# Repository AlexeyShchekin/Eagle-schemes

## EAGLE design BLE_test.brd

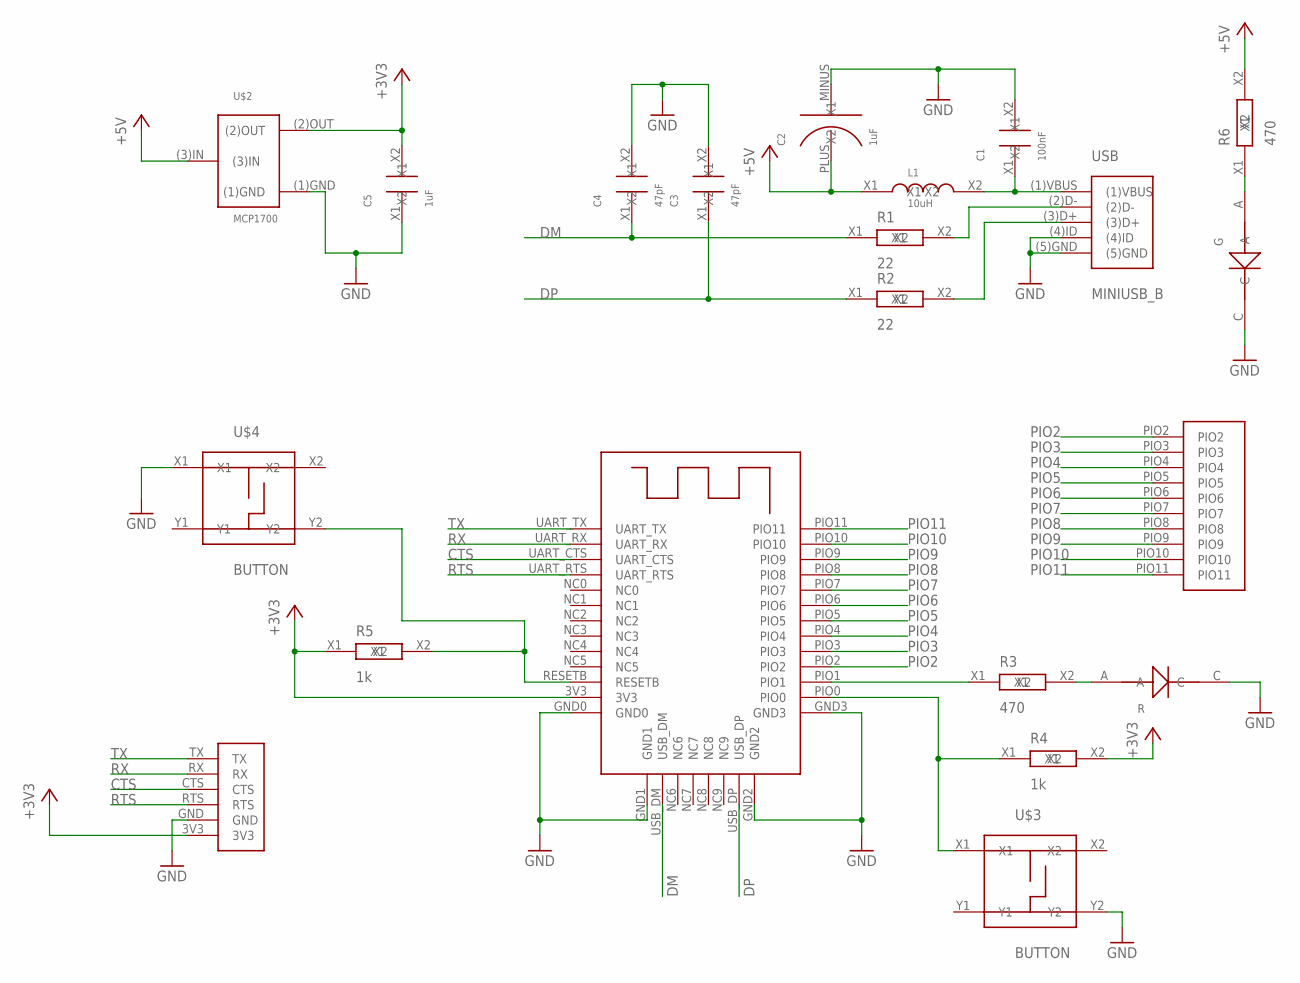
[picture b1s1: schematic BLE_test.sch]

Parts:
C1: 100nF; SMD_2.1X1.25
C2: 1uF; C_SMD_TA_A
C3, C4: 47pF; SMD_2.1X1.25
C5: 1uF; SMD_2.1X1.25
G: LED0805; SMD0805
L1: 10uH; SMD_2.1X1.25
R: LED0805; SMD0805
R1, R2: 22; SMD_2.1X1.25
R3, R6: 470; SMD_2.1X1.25
R4, R5: 1k; SMD_2.1X1.25
U$1: BLE_HM10
U$2: MCP1700
U$3, U$4: BUTTON
U$5: PIN6
U$7: PIO_10
USB: MINIUSB_B

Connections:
+3V3: C5.X2, R4.X2, R5.X1, U$1.3V3, U$2.(2)OUT, U$5.3V3
+5V: C2.PLUS (X1), L1.X1, R6.X2, U$2.(3)IN
CTS: U$1.UART_CTS, U$5.CTS
DM: C4.X1, R1.X1, U$1.USB_DM
DP: C3.X1, R2.X1, U$1.USB_DP
GND: C1.X2, C2.MINUS (X2), C3.X2, C4.X2, C5.X1, G.C, R.C, U$1.GND0, U$1.GND1, U$1.GND2, U$1.GND3, U$2.(1)GND, U$3.Y2, U$4.X1, U$5.GND, USB.(4)ID, USB.(5)GND
unnamed: C1.X1, L1.X2, USB.(1)VBUS
unnamed: R2.X2, USB.(3)D+
unnamed: R1.X2, USB.(2)D-
unnamed: R3.X1, U$1.PIO1
unnamed: R.A, R3.X2
unnamed: R4.X1, U$1.PIO0, U$3.X1
unnamed: G.A, R6.X1
unnamed: R5.X2, U$1.RESETB, U$4.Y2
PIO2: U$1.PIO2, U$7.PIO2
PIO3: U$1.PIO3, U$7.PIO3
PIO4: U$1.PIO4, U$7.PIO4
PIO5: U$1.PIO5, U$7.PIO5
PIO6: U$1.PIO6, U$7.PIO6
PIO7: U$1.PIO7, U$7.PIO7
PIO8: U$1.PIO8, U$7.PIO8
PIO9: U$1.PIO9, U$7.PIO9
PIO10: U$1.PIO10, U$7.PIO10
PIO11: U$1.PIO11, U$7.PIO11
RTS: U$1.UART_RTS, U$5.RTS
RX: U$1.UART_RX, U$5.RX
TX: U$1.UART_TX, U$5.TX

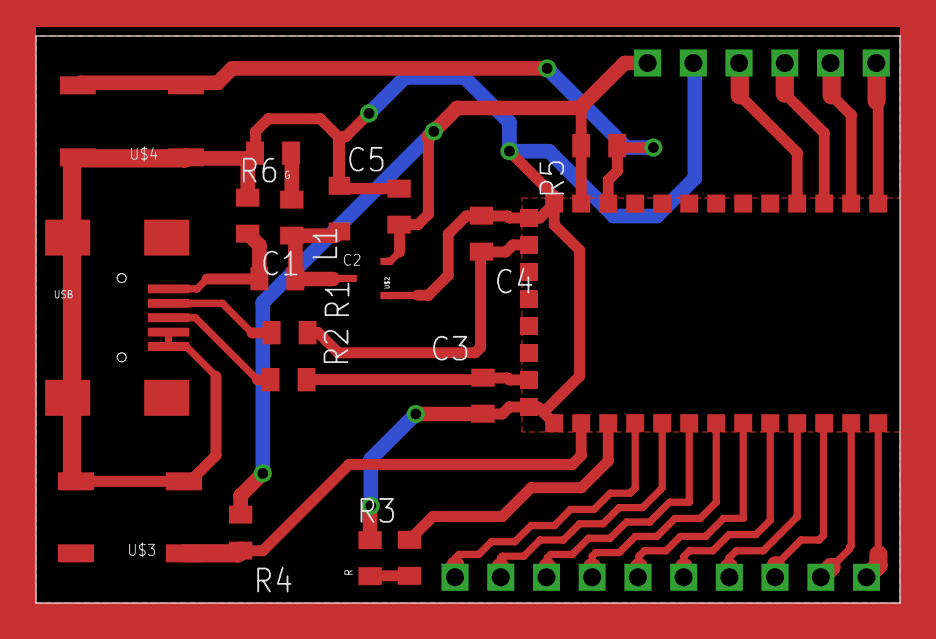
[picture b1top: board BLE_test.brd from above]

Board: 2 copper layers, 48.0 x 31.5 mm, 21 parts (0 on the bottom side), 27 nets.

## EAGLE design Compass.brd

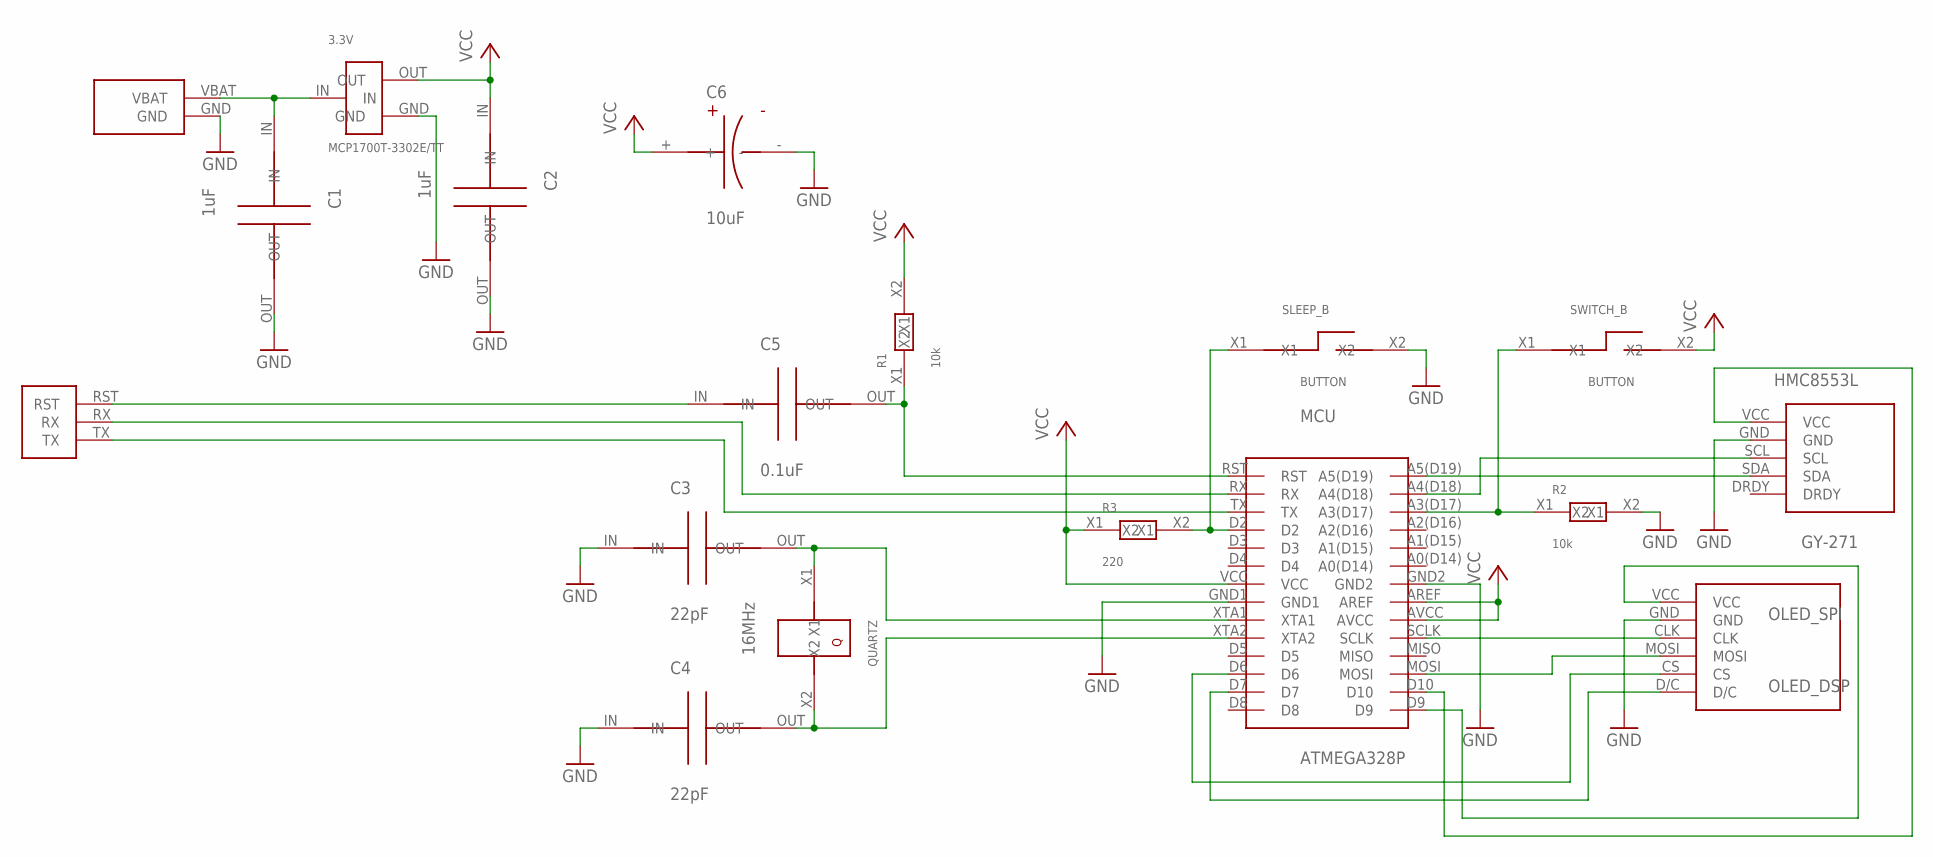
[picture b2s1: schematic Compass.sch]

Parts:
3.3V: MCP1700T-3302E/TT
C1, C2: 1uF; C_CER_5MM
C3, C4: 22pF; C_CER_5MM
C5: 0.1uF; C_CER_5MM
C6: 10uF; C_ELT_2MM
HMC8553L: GY-271
MCU: ATMEGA328P; DIP28
OLED_SPI: OLED_DSP
QUARTZ: 16MHz; Q_16
R1, R2: 10k; R_6X2
R3: 220; R_6X2
SLEEP_B: BUTTON
SWITCH_B: BUTTON
U$1: PROG_PLUG
U$6: BAT_PLUG

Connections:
GND: 3.3V.GND, C1.OUT, C2.OUT, C3.IN, C4.IN, C6.-, HMC8553L.GND, MCU.GND1, MCU.GND2, OLED_SPI.GND, R2.X2, SLEEP_B.X2, U$6.GND
unnamed: MCU.SCLK, OLED_SPI.CLK
unnamed: MCU.MOSI, OLED_SPI.MOSI
unnamed: HMC8553L.SDA, MCU.A5(D19)
unnamed: HMC8553L.SCL, MCU.A4(D18)
unnamed: 3.3V.IN, C1.IN, U$6.VBAT
unnamed: MCU.D9, OLED_SPI.VCC
unnamed: C3.OUT, MCU.XTA1, QUARTZ.X1
unnamed: C4.OUT, MCU.XTA2, QUARTZ.X2
unnamed: MCU.D6, OLED_SPI.CS
unnamed: MCU.D7, OLED_SPI.D/C
unnamed: HMC8553L.VCC, MCU.D10
unnamed: C5.OUT, MCU.RST, R1.X1
unnamed: MCU.D2, R3.X2, SLEEP_B.X1
unnamed: MCU.A3(D17), R2.X1, SWITCH_B.X1
unnamed: C5.IN, U$1.RST
unnamed: MCU.RX, U$1.RX
unnamed: MCU.TX, U$1.TX
VCC: 3.3V.OUT, C2.IN, C6.+, MCU.AREF, MCU.AVCC, MCU.VCC, R1.X2, R3.X1, SWITCH_B.X2

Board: 2 copper layers, 18 parts (0 on the bottom side), 19 nets, no tracks yet.

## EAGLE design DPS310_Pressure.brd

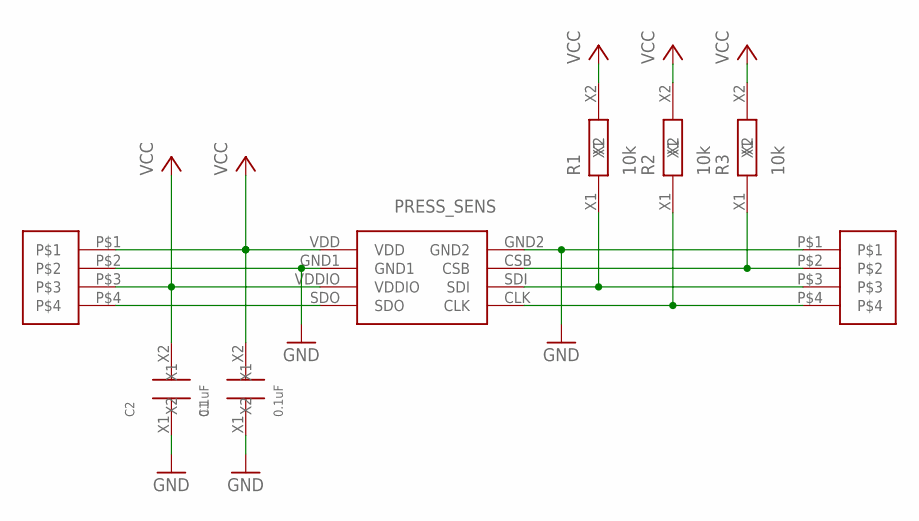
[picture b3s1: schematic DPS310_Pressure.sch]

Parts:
C1, C2: 0.1uF; SMD_2.1X1.25
PRESS_SENS: DPS310_INFINEON; DSP310
R1, R2, R3: 10k; SMD_2.1X1.25
U$1, U$2: 4-PIN-NONAME

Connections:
GND: C1.X1, C2.X1, PRESS_SENS.GND1, PRESS_SENS.GND2, U$1.P$1, U$2.P$2
unnamed: PRESS_SENS.CSB, R3.X1, U$1.P$2
unnamed: PRESS_SENS.SDI, R1.X1, U$1.P$3
unnamed: PRESS_SENS.CLK, R2.X1, U$1.P$4
unnamed: PRESS_SENS.SDO, U$2.P$4
VCC: C1.X2, C2.X2, PRESS_SENS.VDD, PRESS_SENS.VDDIO, R1.X2, R2.X2, R3.X2, U$2.P$1, U$2.P$3

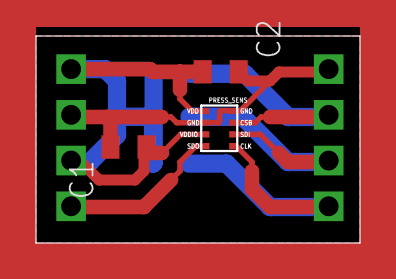
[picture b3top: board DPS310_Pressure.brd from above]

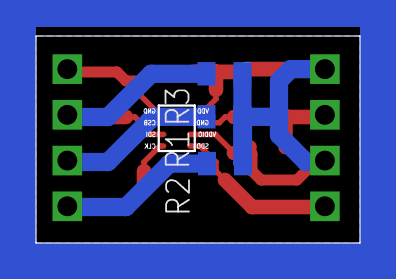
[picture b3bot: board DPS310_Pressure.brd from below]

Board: 2 copper layers, 18.0 x 11.5 mm, 8 parts (3 on the bottom side), 6 nets.

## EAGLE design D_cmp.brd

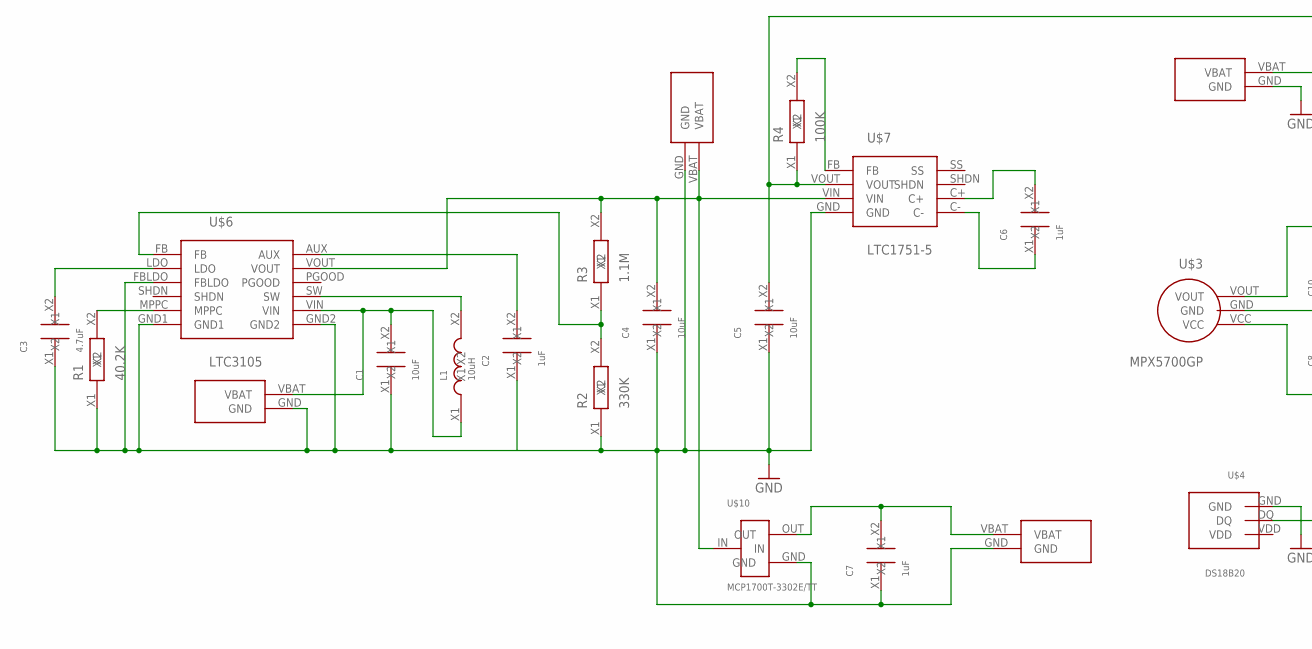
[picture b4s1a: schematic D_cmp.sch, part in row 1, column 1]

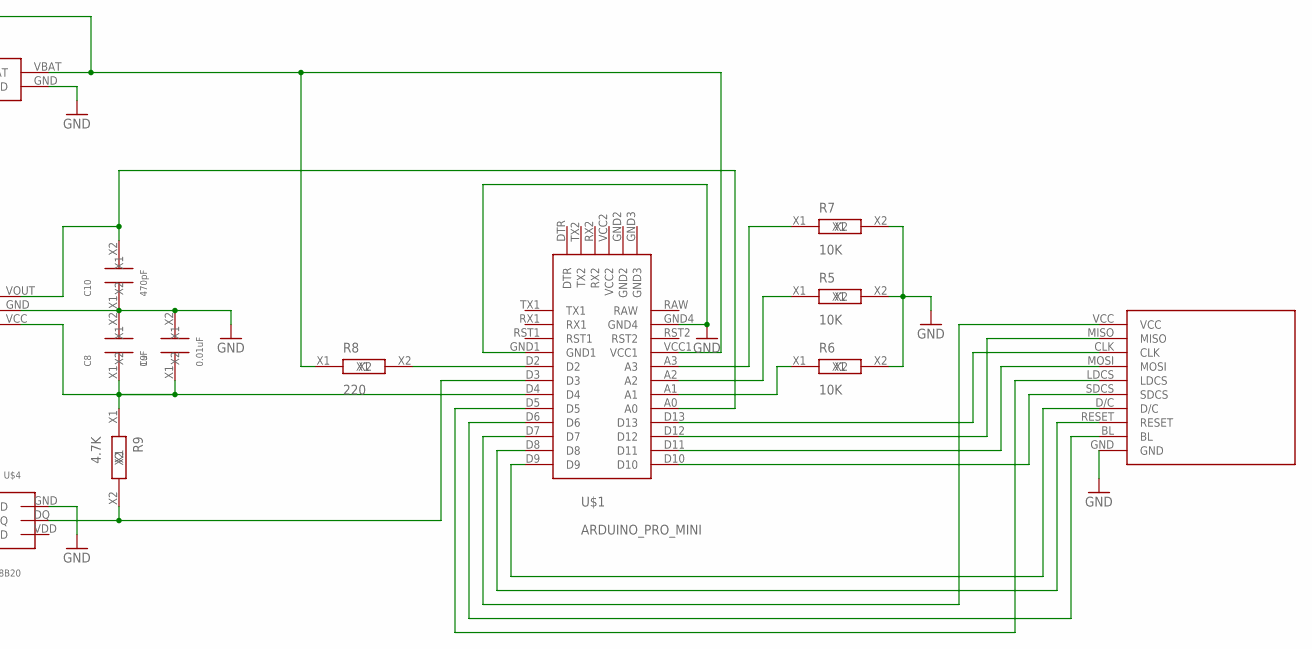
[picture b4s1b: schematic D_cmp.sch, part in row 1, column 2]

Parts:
C1, C4, C5: 10uF; SMD_2.1X1.25
C2, C6, C7, C8: 1uF; SMD_2.1X1.25
C3: 4.7uF; SMD_2.1X1.25
C9: 0.01uF; SMD_2.1X1.25
C10: 470pF; SMD_2.1X1.25
L1: 10uH; SMD_2.1X1.25
R1: 40.2K; SMD_2.1X1.25
R2: 330K; SMD_2.1X1.25
R3: 1.1M; SMD_2.1X1.25
R4: 100K; SMD_2.1X1.25
R5, R6, R7: 10K; SMD_2.1X1.25
R8: 220; SMD_2.1X1.25
R9: 4.7K; SMD_2.1X1.25
U$1: ARDUINO_PRO_MINI
U$2: TFT_LCD
U$3: MPX5700GP
U$4: DS18B20
U$5, U$8, U$9, U$11: BAT_PLUG
U$6: LTC3105
U$7: LTC1751-5
U$10: MCP1700T-3302E/TT

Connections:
GND: C1.X1, C2.X1, C3.X1, C4.X1, C5.X1, C7.X1, C8.X2, C9.X2, C10.X1, R1.X1, R2.X1, R5.X2, R6.X2, R7.X2, U$1.GND1, U$1.GND4, U$2.GND, U$3.GND, U$4.GND, U$5.GND, U$6.FBLDO, U$6.GND1, U$6.GND2, U$7.GND, U$8.GND, U$9.GND, U$10.GND, U$11.GND
unnamed: U$1.D9, U$2.D/C
unnamed: U$1.D8, U$2.RESET
unnamed: U$1.D10, U$2.SDCS
unnamed: U$1.D11, U$2.MOSI
unnamed: U$1.D12, U$2.MISO
unnamed: U$1.D13, U$2.CLK
unnamed: U$1.D7, U$2.VCC
unnamed: U$1.D6, U$2.BL
unnamed: R6.X1, U$1.A1
unnamed: R5.X1, U$1.A2
unnamed: R7.X1, U$1.A3
unnamed: R8.X2, U$1.D2
unnamed: C8.X1, C9.X1, R9.X1, U$1.D4, U$3.VCC
unnamed: R9.X2, U$1.D3, U$4.DQ
unnamed: C10.X2, U$1.A0, U$3.VOUT
unnamed: R1.X2, U$6.MPPC
unnamed: C3.X2, U$6.LDO
unnamed: L1.X2, U$6.SW
unnamed: C2.X2, U$6.AUX
unnamed: R2.X2, R3.X1, U$6.FB
unnamed: C1.X2, L1.X1, U$6.VIN, U$8.VBAT
unnamed: C4.X2, R3.X2, U$6.VOUT, U$7.VIN, U$9.VBAT, U$10.IN
unnamed: C5.X2, R4.X1, R8.X1, U$1.VCC1, U$5.VBAT, U$7.VOUT
unnamed: R4.X2, U$7.FB
unnamed: C6.X1, U$7.C-
unnamed: C6.X2, U$7.C+
unnamed: C7.X2, U$10.OUT, U$11.VBAT
unnamed: U$1.D5, U$2.LDCS

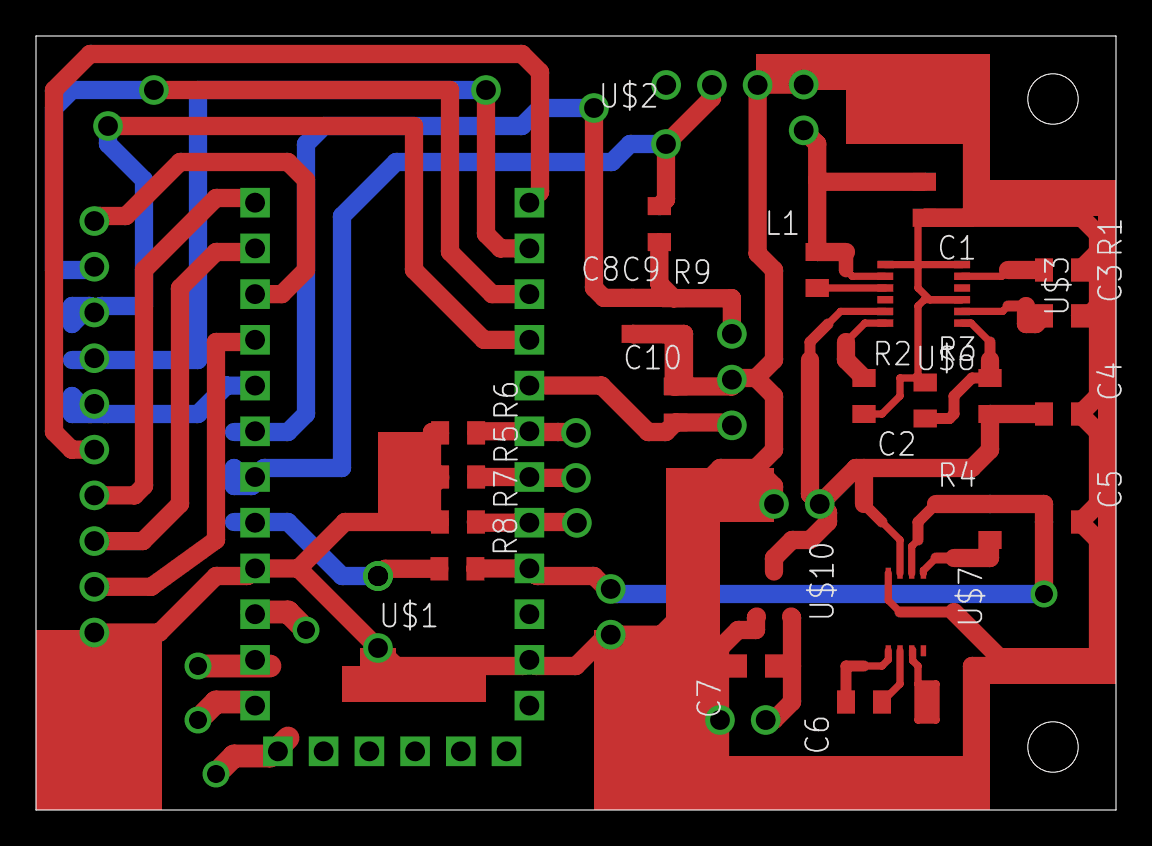
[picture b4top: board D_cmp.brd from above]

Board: 2 copper layers, 60.0 x 43.0 mm, 31 parts (0 on the bottom side), 29 nets.

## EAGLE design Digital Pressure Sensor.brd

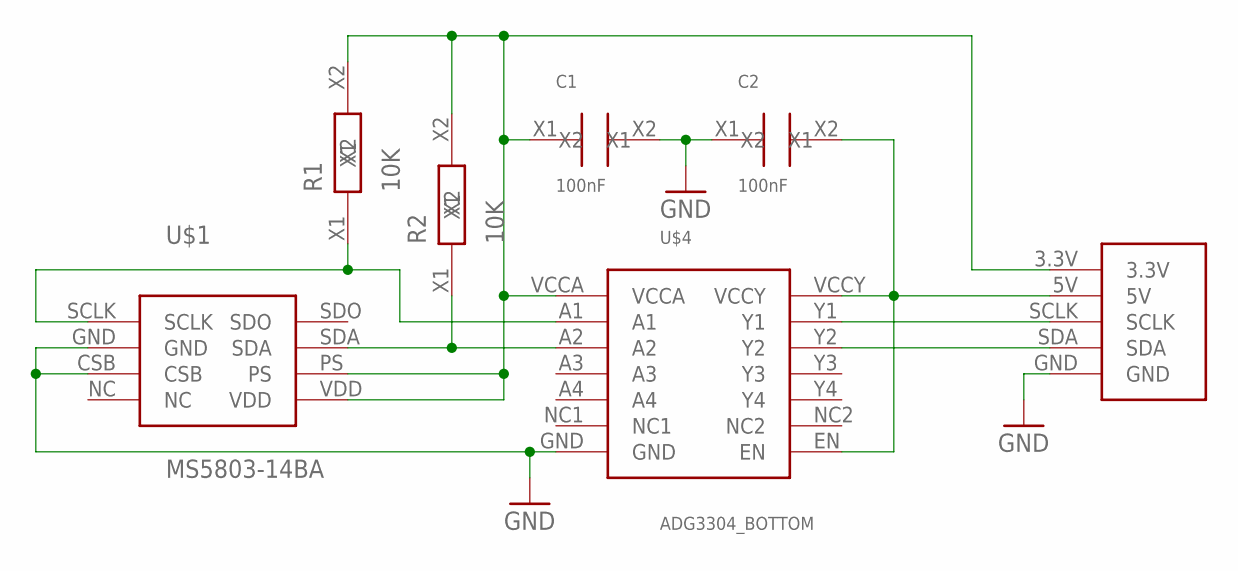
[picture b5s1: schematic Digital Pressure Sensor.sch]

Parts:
C1, C2: 100nF; SMD_2.1X1.25_BOTTOM
R1, R2: 10K; SMD_2.1X1.25_BOTTOM
U$1: MS5803-14BA
U$3: 5-PIN-PLUG
U$4: ADG3304_BOTTOM

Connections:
GND: C1.X2, C2.X1, U$1.CSB, U$1.GND, U$3.GND, U$4.GND
unnamed: R2.X1, U$1.SDA, U$4.A2
unnamed: R1.X1, U$1.SCLK, U$4.A1
unnamed: U$3.SCLK, U$4.Y1
unnamed: C1.X1, R1.X2, R2.X2, U$1.PS, U$1.VDD, U$3.3.3V, U$4.VCCA
unnamed: C2.X2, U$3.5V, U$4.EN, U$4.VCCY
unnamed: U$3.SDA, U$4.Y2

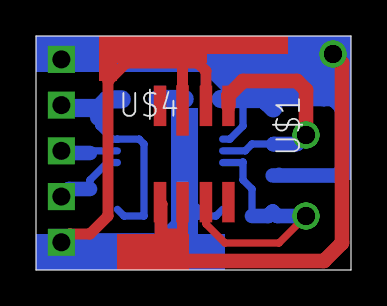
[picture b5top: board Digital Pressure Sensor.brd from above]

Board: 2 copper layers, 17.5 x 13.0 mm, 7 parts (0 on the bottom side), 7 nets.

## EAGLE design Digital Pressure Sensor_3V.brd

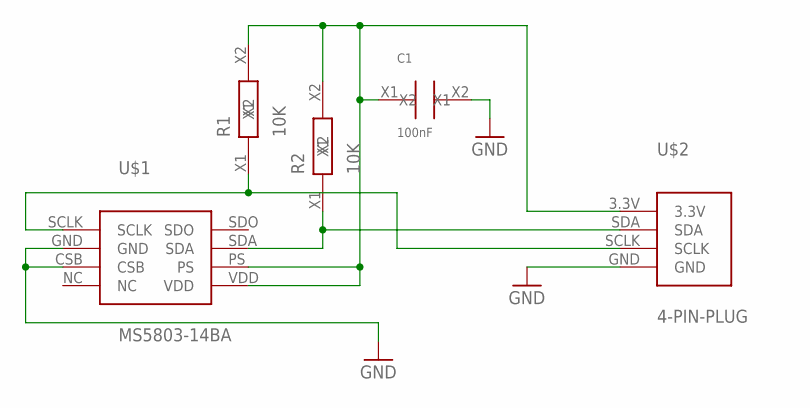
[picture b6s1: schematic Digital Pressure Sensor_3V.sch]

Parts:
C1: 100nF; SMD_2.1X1.25_BOTTOM
R1, R2: 10K; SMD_2.1X1.25_BOTTOM
U$1: MS5803-14BA
U$2: 4-PIN-PLUG

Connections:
GND: C1.X2, U$1.CSB, U$1.GND, U$2.GND
unnamed: R2.X1, U$1.SDA, U$2.SDA
unnamed: R1.X1, U$1.SCLK, U$2.SCLK
unnamed: C1.X1, R1.X2, R2.X2, U$1.PS, U$1.VDD, U$2.3.3V

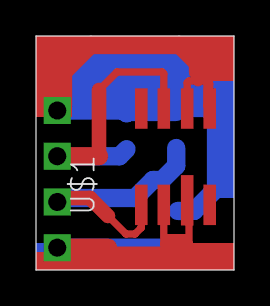
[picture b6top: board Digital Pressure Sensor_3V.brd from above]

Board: 2 copper layers, 11.0 x 13.0 mm, 5 parts (0 on the bottom side), 4 nets.

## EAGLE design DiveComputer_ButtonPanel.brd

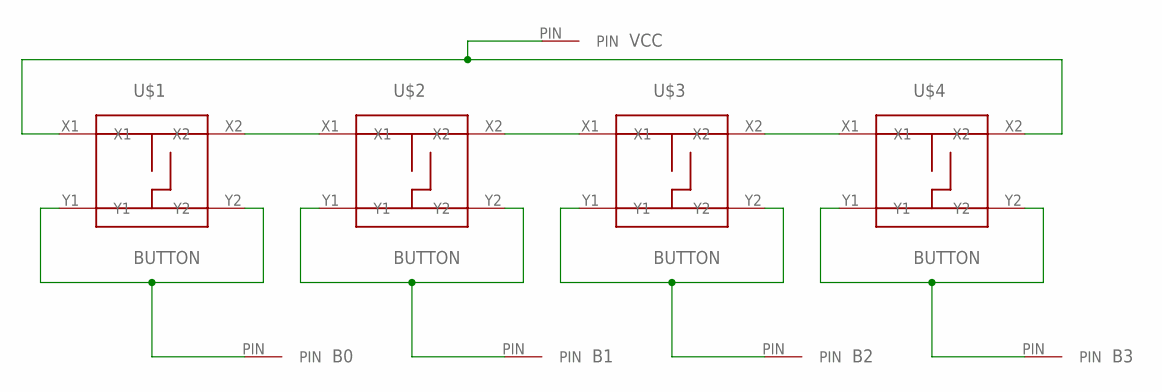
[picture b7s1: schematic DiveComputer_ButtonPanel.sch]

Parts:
B0, B1, B2, B3: PIN
U$1, U$2, U$3, U$4: BUTTON
VCC: PIN

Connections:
B0: B0.PIN, U$1.Y1, U$1.Y2
B1: B1.PIN, U$2.Y1, U$2.Y2
B2: B2.PIN, U$3.Y1, U$3.Y2
B3: B3.PIN, U$4.Y1, U$4.Y2
VCC: U$1.X1, U$1.X2, U$2.X1, U$2.X2, U$3.X1, U$3.X2, U$4.X1, U$4.X2, VCC.PIN

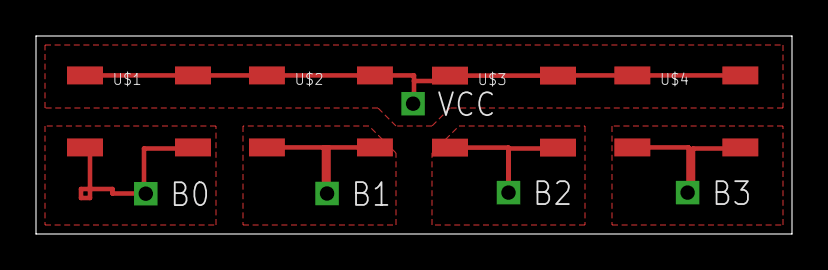
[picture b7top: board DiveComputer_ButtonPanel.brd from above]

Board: 2 copper layers, 42.0 x 11.0 mm, 9 parts (0 on the bottom side), 5 nets.
